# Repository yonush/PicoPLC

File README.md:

# The RP2040/RP2350 PLC - picoPLC

This repo is the design files and sample code for the diy PLC "picoPLC". It is robust PLC using the Raspberry Pi microcontroller boards as the main controller. Supported boards:

- Raspberry Pico (RP2040)
- Raspberry Pico W (RP2040)
- Raspberry Pico 2 (RP2350 using ARM cores)
- Raspberry Pico 2 (RP2350 using RISC-V cores)

Other RP2040/RP2350 boards that follow the Raspberry Pico pinout are also supported

The picoPLC has the following features 

- 5-12V power (connections are 12V tolerant. NO 24V)
- Has a 3.3, 5V and 12V breakout (if 12V power used)
- 8 digital outputs using relays
- 8 digital inputs
- 3 analog inputs
- 2 analog outputs (PWM or analog)
- 1 1-wire (Dallas/DHT22/DHT11, etc)
- 1 I2C, SPI, UART (shared pins)

The picoPLC was originally designed to use the [OpenPLC](https://autonomylogic.com/) soft PLC but it has been tested with C/C++, MicroPython and CircuitPython. Sample code for the CircuitPython has been included. The demo CircuitPython code uses [pyRTOS](https://github.com/Rybec/pyRTOS) as a proof of concept for some asynchronous tasks. 

### Mutli-core operation

Multi-core operation is not supported in CircuitPython but is available using MicroPython. Multi-core operation can be achieved in OpenPLC by editing the HAL source files and using the Mbed OS toolchain. More details on Using OpenPLC can be found in [OpenPLC Notes](OpenPLC_notes.md)

### TODO
- :white_check_mark: Fix PWM range and frequency (rev2)
- :white_large_square: Revision 3 to support 24V inputs
- :white_large_square: Revision 3 to include opto-isolaters on the inputs
- :white_large_square: Additional sample code

## Schematic
Schematic was created in KiCad. The BoM can be found in **Schematic and PCB** folder. The image below is only of page 1. Full schematic can be found in the folder.

### Physical device

**Revison 1**

**Revison 2**

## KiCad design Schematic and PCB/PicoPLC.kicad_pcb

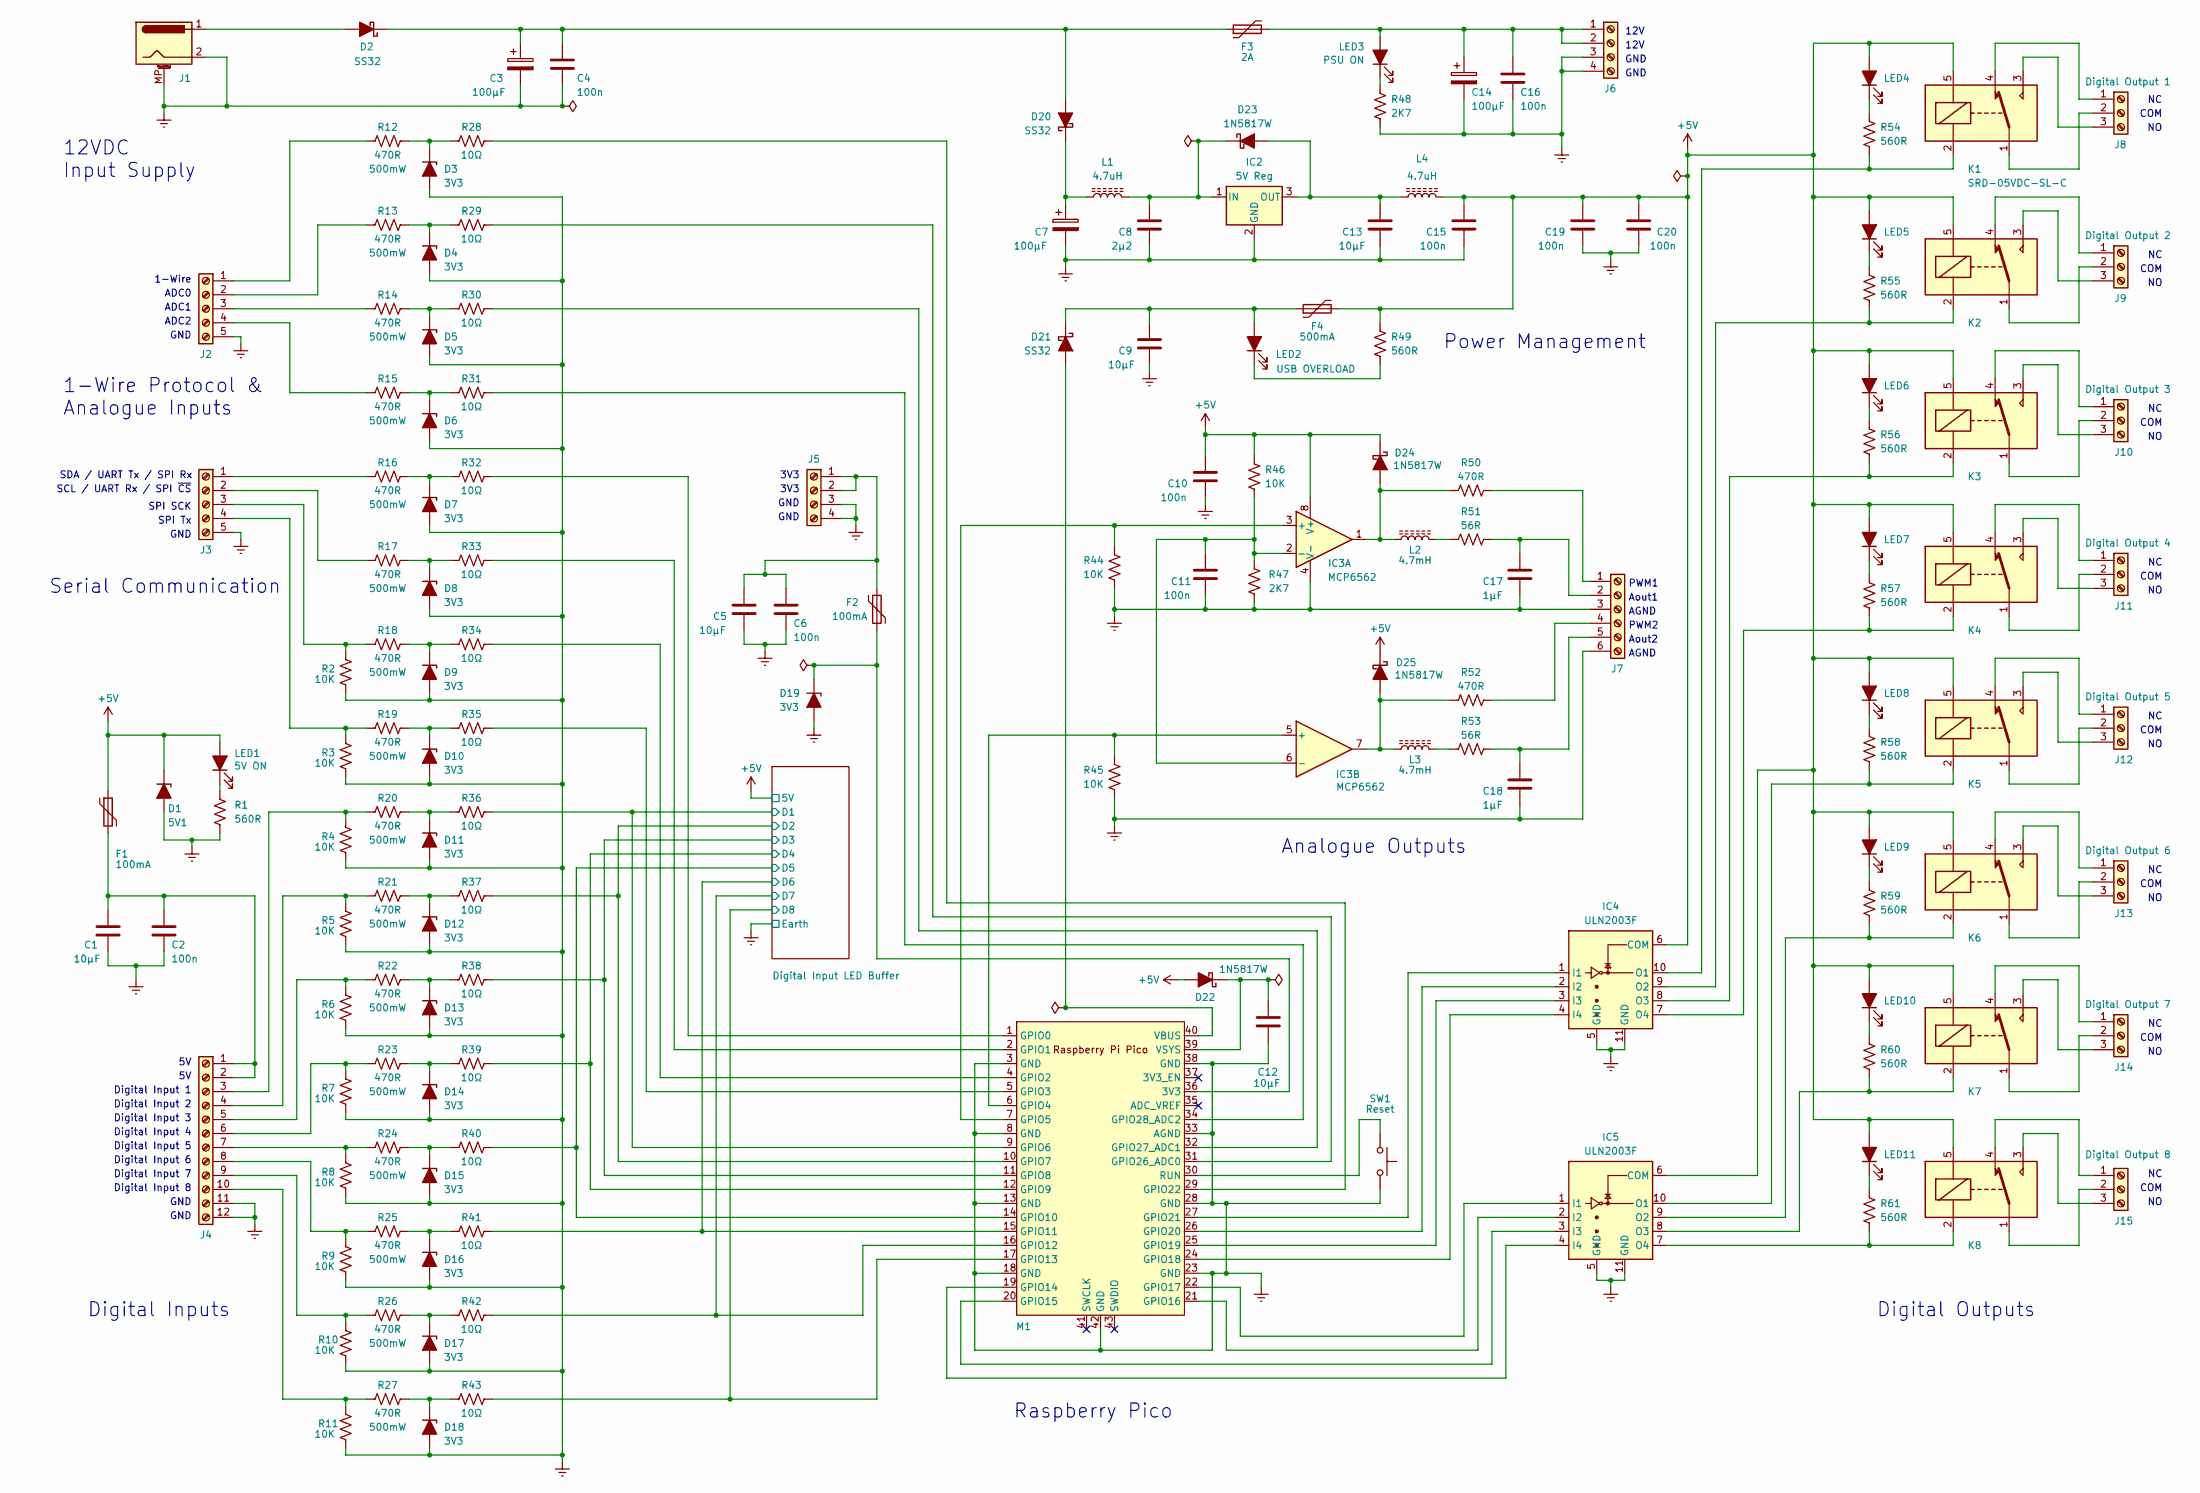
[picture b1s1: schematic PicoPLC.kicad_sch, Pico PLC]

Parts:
C1, C5, C9, C12, C13: 10µF; C_1206_3216Metric
C2, C4, C6, C10, C11, C15, C16, C19, C20: 100n; C_0805_2012Metric
C3, C7, C14: 100µF; CP_Elec_6.3x7.7
C8: 2µ2; C_0805_2012Metric
C17, C18: 1µF; C_0805_2012Metric
D1: 5V1; D_SOD-123
D2, D20, D21: SS32; D_SMA
D3, D4, D5, D6, D7, D8, D9, D10, D11, D12, D13, D14, D15, D16, D17, D18, D19: 3V3; D_SOD-123
D22, D23, D24, D25: 1N5817W; D_0805_2012Metric
F1, F2: 100mA; Fuse_0805_2012Metric
F3: 2A; Fuse_0805_2012Metric
F4: 500mA; Fuse_0805_2012Metric
IC2: 5V Reg; Converter_DCDC_RECOM_R-78E-0.5_THT
IC3: MCP6562; MSOP-8_3x3mm_P0.65mm
IC4, IC5: ULN2003F; DFN-10-1EP_3x3mm_P0.5mm_EP1.65x2.38mm
J1: 2.1/5.5mm Jack; BarrelJack_CUI_PJ-063AH_Horizontal
J2, J3: Screw_Terminal_01x05; Terminal_KF142V_Spring_5.08mm_V_5Pole
J4: Screw_Terminal_01x12; Terminal_KF142V_Spring_5.08mm_V_12Pole
J5, J6: Screw_Terminal_01x04; Terminal_KF142V_Spring_5.08mm_V_4Pole
J7: Screw_Terminal_01x06; Terminal_KF142V_Spring_5.08mm_V_6Pole
J8, J9, J10, J11, J12, J13, J14, J15: Screw_Terminal_01x03; Terminal_KF142V_Spring_5.08mm_V_3Pole
K1, K2, K3, K4, K5, K6, K7, K8: SRD-05VDC-SL-C; Relay_SPDT_SANYOU_SRD_Series_Form_C
L1, L4: 4.7uH; IND_Bourns_SRN5020; Part SRN5020TA-5R6M
L2, L3: 4.7mH; IND_Bourns_SDR0503
LED1, LED4, LED5, LED6, LED7, LED8, LED9, LED10, LED11: LED_Filled; LED_0805_2012Metric
LED2: USB OVERLOAD; LED_0805_2012Metric
LED3: PSU ON; LED_0805_2012Metric
M1: Pico; RPi_Pico_SMD_TH
R1, R49, R54, R55, R56, R57, R58, R59, R60, R61: 560R; R_0805_2012Metric
R2, R3, R4, R5, R6, R7, R8, R9, R10, R11, R44, R45, R46: 10K; R_0805_2012Metric
R12, R13, R14, R15, R16, R17, R18, R19, R20, R21, R22, R23, R24, R25, R26, R27, R50, R52: 470R; R_0805_2012Metric
R28, R29, R30, R31, R32, R33, R34, R35, R36, R37, R38, R39, R40, R41, R42, R43: 10Ω; R_0805_2012Metric
R47, R48: 2K7; R_0805_2012Metric
R51, R53: 56R; R_0805_2012Metric
SW1: Reset; SW_Tactile_SPST_Angled_PTS645Vx58-2LFS

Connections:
+5V: C10.1, C15.1, C19.1, C20.1, D1.1 (K), D22.2 (A), D24.1 (K), D25.1 (K), F1.1, F4.2, IC3.8 (V+), IC4.6 (COM), IC5.6 (COM), K1.5, K2.5, K3.5, K4.5, K5.5, K6.5, K7.5, K8.5, L4.2, LED1.2 (A), LED4.2 (A), LED5.2 (A), LED6.2 (A), LED7.2 (A), LED8.2 (A), LED9.2 (A), LED10.2 (A), LED11.2 (A), R46.2, R49.1; also elsewhere on the board
/Digital Input LED Buffer/D1: M1.9 (GPIO6), R36.2; also elsewhere on the board
/Digital Input LED Buffer/D2: M1.10 (GPIO7), R37.2; also elsewhere on the board
/Digital Input LED Buffer/D3: M1.11 (GPIO8), R38.2; also elsewhere on the board
/Digital Input LED Buffer/D4: M1.12 (GPIO9), R39.2; also elsewhere on the board
/Digital Input LED Buffer/D5: M1.14 (GPIO10), R40.2; also elsewhere on the board
/Digital Input LED Buffer/D6: M1.15 (GPIO11), R41.2; also elsewhere on the board
/Digital Input LED Buffer/D7: M1.16 (GPIO12), R42.2; also elsewhere on the board
/Digital Input LED Buffer/D8: M1.17 (GPIO13), R43.2; also elsewhere on the board
Earth: C1.2, C2.2, C3.2, C4.2, C5.2, C6.2, C7.2, C8.2, C9.2, C10.2, C11.2, C12.2, C13.2, C14.2, C15.2, C16.2, C17.2, C18.2, C19.2, C20.2, D1.2 (A), D3.2 (A), D4.2 (A), D5.2 (A), D6.2 (A), D7.2 (A), D8.2 (A), D9.2 (A), D10.2 (A), D11.2 (A), D12.2 (A), D13.2 (A), D14.2 (A), D15.2 (A), D16.2 (A), D17.2 (A), D18.2 (A), D19.2 (A), IC2.2 (GND), IC3.4 (V-), IC4.5 (GND), IC4.11 (GND), IC5.5 (GND), IC5.11 (GND), J1.2, J1.MP (MountPin), J2.5, J3.5, J4.11, J4.12, J5.3, J5.4, J6.3, J6.4, J7.3, J7.6, M1.3 (GND), M1.8 (GND), M1.13 (GND), M1.18 (GND), M1.23 (GND), M1.28 (GND), M1.33 (AGND), M1.38 (GND), M1.42 (GND), R1.2, R2.2, R3.2, R4.2, R5.2, R6.2, R7.2, R8.2, R9.2, R10.2, R11.2, R44.1, R45.1, R47.1, R48.2, SW1.2; also elsewhere on the board
unnamed: D2.2 (A), J1.1
unnamed: C3.1, C4.1, D2.1 (K), D20.2 (A), F3.1
unnamed: D3.1 (K), R12.2, R28.1
unnamed: D4.1 (K), R13.2, R29.1
unnamed: D5.1 (K), R14.2, R30.1
unnamed: D6.1 (K), R15.2, R31.1
unnamed: D7.1 (K), R16.2, R32.1
unnamed: D8.1 (K), R17.2, R33.1
unnamed: D9.1 (K), R18.2, R34.1
unnamed: D10.1 (K), R19.2, R35.1
unnamed: D11.1 (K), R20.2, R36.1
unnamed: D12.1 (K), R21.2, R37.1
unnamed: D13.1 (K), R22.2, R38.1
unnamed: D14.1 (K), R23.2, R39.1
unnamed: D15.1 (K), R24.2, R40.1
unnamed: D16.1 (K), R25.2, R41.1
unnamed: D17.1 (K), R26.2, R42.1
unnamed: D18.1 (K), R27.2, R43.1
unnamed: D19.1 (K), F2.2, M1.36 (3V3)
unnamed: C7.1, D20.1 (K), L1.1
unnamed: D21.2 (A), M1.40 (VBUS)
unnamed: C9.1, D21.1 (K), F4.1, LED2.2 (A)
unnamed: C12.1, D22.1 (K), M1.39 (VSYS)
unnamed: C13.1, D23.2 (A), IC2.3 (OUT), L4.1
unnamed: C8.1, D23.1 (K), IC2.1 (IN), L1.2
unnamed: D24.2 (A), IC3.1, L2.1, R50.1
unnamed: D25.2 (A), IC3.7, L3.1, R52.1
unnamed: IC3.3 (+), M1.7 (GPIO5), R44.2
unnamed: C11.1, IC3.2 (-), IC3.6 (-), R46.1, R47.2
unnamed: IC3.5 (+), M1.6 (GPIO4), R45.2
unnamed: IC4.1 (I1), M1.27 (GPIO21)
unnamed: IC4.2 (I2), M1.26 (GPIO20)
unnamed: IC4.3 (I3), M1.25 (GPIO19)
unnamed: IC4.4 (I4), M1.24 (GPIO18)
unnamed: IC4.10 (O1), K1.2, R54.2
unnamed: IC4.9 (O2), K2.2, R55.2
unnamed: IC4.8 (O3), K3.2, R56.2
unnamed: IC4.7 (O4), K4.2, R57.2
unnamed: IC5.1 (I1), M1.22 (GPIO17)
unnamed: IC5.2 (I2), M1.21 (GPIO16)
unnamed: IC5.3 (I3), M1.20 (GPIO15)
unnamed: IC5.4 (I4), M1.19 (GPIO14)
unnamed: IC5.10 (O1), K5.2, R58.2
unnamed: IC5.9 (O2), K6.2, R59.2
unnamed: IC5.8 (O3), K7.2, R60.2
unnamed: IC5.7 (O4), K8.2, R61.2
unnamed: J2.1, R12.1
unnamed: J2.2, R13.1
unnamed: J2.3, R14.1
unnamed: J2.4, R15.1
unnamed: J3.1, R16.1
unnamed: J3.2, R17.1
unnamed: J3.3, R2.1, R18.1
unnamed: J3.4, R3.1, R19.1
unnamed: C1.1, C2.1, F1.2, J4.1, J4.2
unnamed: J4.3, R4.1, R20.1
unnamed: J4.4, R5.1, R21.1
unnamed: J4.5, R6.1, R22.1
unnamed: J4.6, R7.1, R23.1
unnamed: J4.7, R8.1, R24.1
unnamed: J4.8, R9.1, R25.1
unnamed: J4.9, R10.1, R26.1
unnamed: J4.10, R11.1, R27.1
unnamed: C5.1, C6.1, F2.1, J5.1, J5.2
unnamed: C14.1, C16.1, F3.2, J6.1, J6.2, LED3.2 (A)
unnamed: J7.1, R50.2
unnamed: C17.1, J7.2, R51.1
unnamed: J7.4, R52.2
unnamed: C18.1, J7.5, R53.1
unnamed: J8.1, K1.4
unnamed: J8.2, K1.1
unnamed: J8.3, K1.3
unnamed: J9.1, K2.4
unnamed: J9.2, K2.1
unnamed: J9.3, K2.3
unnamed: J10.1, K3.4
unnamed: J10.2, K3.1
unnamed: J10.3, K3.3
unnamed: J11.1, K4.4
unnamed: J11.2, K4.1
unnamed: J11.3, K4.3
unnamed: J12.1, K5.4
unnamed: J12.2, K5.1
unnamed: J12.3, K5.3
unnamed: J13.1, K6.4
unnamed: J13.2, K6.1
unnamed: J13.3, K6.3
unnamed: J14.1, K7.4
unnamed: J14.2, K7.1
unnamed: J14.3, K7.3
unnamed: J15.1, K8.4
unnamed: J15.2, K8.1
unnamed: J15.3, K8.3
unnamed: L2.2, R51.2
unnamed: L3.2, R53.2
unnamed: LED1.1 (K), R1.1
unnamed: LED2.1 (K), R49.2
unnamed: LED3.1 (K), R48.1
unnamed: LED4.1 (K), R54.1
unnamed: LED5.1 (K), R55.1
unnamed: LED6.1 (K), R56.1
unnamed: LED7.1 (K), R57.1
unnamed: LED8.1 (K), R58.1
unnamed: LED9.1 (K), R59.1
unnamed: LED10.1 (K), R60.1
unnamed: LED11.1 (K), R61.1
unnamed: M1.1 (GPIO0), R32.2
unnamed: M1.2 (GPIO1), R33.2
unnamed: M1.4 (GPIO2), R34.2
unnamed: M1.5 (GPIO3), R35.2
unnamed: M1.29 (GPIO22), R28.2
unnamed: M1.31 (GPIO26_ADC0), R29.2
unnamed: M1.32 (GPIO27_ADC1), R30.2
unnamed: M1.34 (GPIO28_ADC2), R31.2
unnamed: M1.30 (RUN), SW1.1

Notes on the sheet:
Aout1
GND
COM
SPI SCK
ADC1
Analogue Outputs
Digital Input 7
SPI Tx
ADC0
3V3
12V
Digital Input 4
Digital Outputs
Digital Input 8
Power Management
Digital Input 5
Digital Input 6
12VDC Input Supply
1-Wire
1-Wire Protocol & Analogue Inputs
Digital Input 2
PWM1
Digital Input 1
ADC2
AGND
Serial Communication
SCL / UART Rx / SPI ~{CS}
SDA / UART Tx / SPI Rx
Digital Input 3
Digital Inputs
Aout2
PWM2
Raspberry Pico

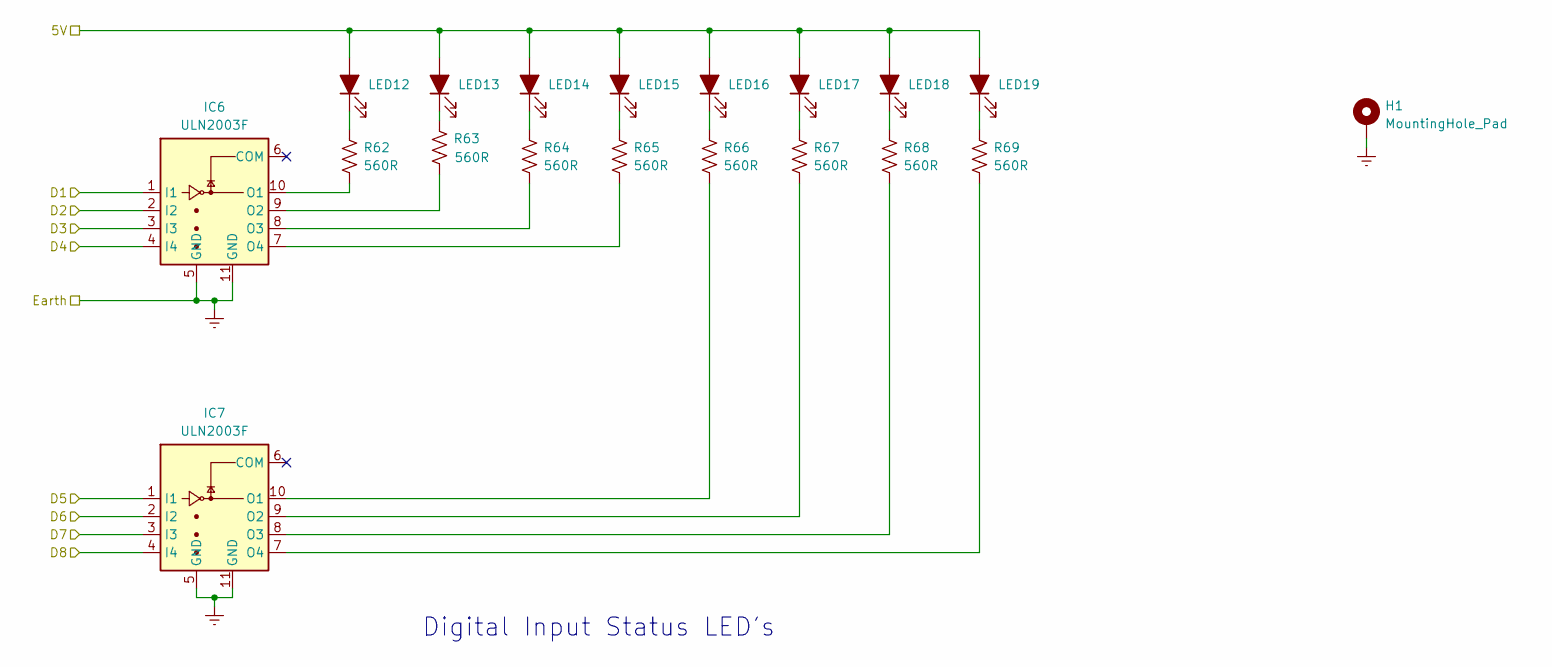
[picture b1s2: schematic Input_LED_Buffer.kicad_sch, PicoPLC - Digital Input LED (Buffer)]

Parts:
H1: MountingHole_Pad; MountingHole_3mm_Pad
IC6, IC7: ULN2003F; DFN-10-1EP_3x3mm_P0.5mm_EP1.65x2.38mm
LED12, LED13, LED14, LED15, LED16, LED17, LED18, LED19: LED_Filled; LED_0805_2012Metric
R62, R63, R64, R65, R66, R67, R68, R69: 560R; R_0805_2012Metric

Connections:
+5V: LED12.2 (A), LED13.2 (A), LED14.2 (A), LED15.2 (A), LED16.2 (A), LED17.2 (A), LED18.2 (A), LED19.2 (A); also elsewhere on the board
/Digital Input LED Buffer/D1: IC6.1 (I1); also elsewhere on the board
/Digital Input LED Buffer/D2: IC6.2 (I2); also elsewhere on the board
/Digital Input LED Buffer/D3: IC6.3 (I3); also elsewhere on the board
/Digital Input LED Buffer/D4: IC6.4 (I4); also elsewhere on the board
/Digital Input LED Buffer/D5: IC7.1 (I1); also elsewhere on the board
/Digital Input LED Buffer/D6: IC7.2 (I2); also elsewhere on the board
/Digital Input LED Buffer/D7: IC7.3 (I3); also elsewhere on the board
/Digital Input LED Buffer/D8: IC7.4 (I4); also elsewhere on the board
Earth: H1.1, IC6.5 (GND), IC6.11 (GND), IC7.5 (GND), IC7.11 (GND); also elsewhere on the board
unnamed: IC6.10 (O1), R62.2
unnamed: IC6.9 (O2), R63.2
unnamed: IC6.8 (O3), R64.2
unnamed: IC6.7 (O4), R65.2
unnamed: IC7.10 (O1), R66.2
unnamed: IC7.9 (O2), R67.2
unnamed: IC7.8 (O3), R68.2
unnamed: IC7.7 (O4), R69.2
unnamed: LED12.1 (K), R62.1
unnamed: LED13.1 (K), R63.1
unnamed: LED14.1 (K), R64.1
unnamed: LED15.1 (K), R65.1
unnamed: LED16.1 (K), R66.1
unnamed: LED17.1 (K), R67.1
unnamed: LED18.1 (K), R68.1
unnamed: LED19.1 (K), R69.1

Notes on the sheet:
Digital Input Status LED's

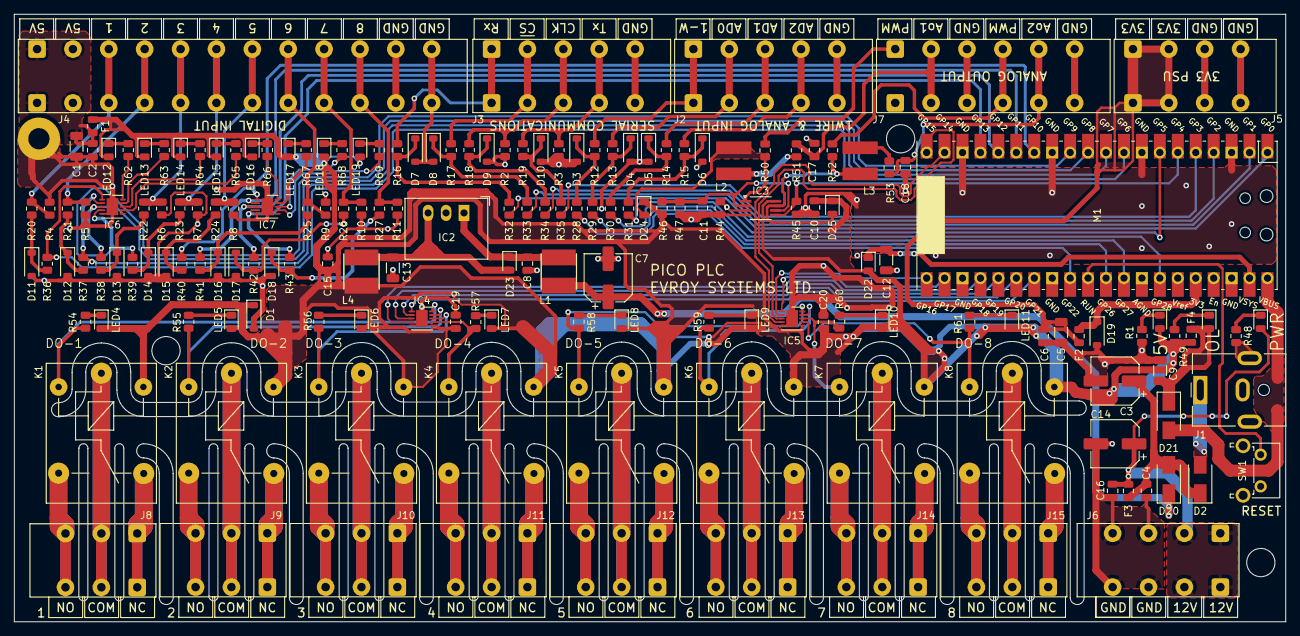
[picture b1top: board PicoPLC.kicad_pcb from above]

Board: 2 copper layers, 180.0 x 86.0 mm, 173 parts (0 on the bottom side), 141 nets.

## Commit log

2024-11-09 Initial repo
2024-11-09 Updated rev2 image, fix typos
2024-11-09 Fix image name...
2024-11-10 Fixed RP2040 title
2024-11-10 fixed numerous typos
2024-11-14 Added some PWM testing
